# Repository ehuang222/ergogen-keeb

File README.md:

# ergogen-keeb (better name pending)
A 66-key wireless (BLE) ergonomic split mechanical keyboard generated with Ergogen. Heavily inspired by [keyzog's Kapl](https://github.com/keyzog/kapl) and [omkbd's Ergodash](https://github.com/omkbd/ErgoDash) keyboards.

This is a learning project. It's _very_ WIP and my first foray into PCB design and 3D modeling. Be warned, stuff in this repo will likely be broken and messy.

## Table of Contents
- [Project Overview](#project-overview)
- [Resources and Tools](#resources-and-tools)
- [Notes](#notes)

## Project Overview
TODO

## Resources and Tools
- [Ergogen Ceoloide](https://ergogen.ceoloide.com/) - Ceoloide's web-based Ergogen that supports custom footprints
- [ceoloide's ergogen PCB footprints](https://github.com/ceoloide/ergogen-footprints) - Very useful to have this open in a separate tab to reference footprint parameters when using the web-based Ergogen
- [FlatFootFox's Let's Design A Keyboard With Ergogen v4](https://flatfootfox.com/ergogen-introduction/) - The de facto Ergogen guide.
- [easyeda2kicad](https://github.com/uPesy/easyeda2kicad.py) - For downloading LSCS (see JLCPCB parts) footprints and models for use in KiCad
- [KiCad to Ergogen footprint converter](https://kicad2ergogen.genteure.com/) - For converting the abovementioned footprints so they can be used in Ceoloide's Ergogen
- [kicad-druid](https://github.com/Cimos/kicad-druid) - KiCad design rules for JLCPCB and PCBWay, supports KiCad versions 8 through 10
- [KiCad ViaStitching Plugin](https://github.com/weirdgyn/viastitching) - Generates stitching vias over a fill zone.
- [SVG Viewer](https://www.svgviewer.dev/) - A web-based SVG viewer, used this to flip/mirror SVG files.
- [Shaper Utilities](https://marketplace.autodesk.com/apps/1caf9b83-5b54-4cab-b893-9c0b9e8f312a) - Autodesk Fusion plugin for exporting SVGs
- [Joric's nrfmicro wiki - Alternatives](https://github.com/joric/nrfmicro/wiki/Alternatives) - Wiki for Pro Micro Compatible alternatives including the SuperMini NRF52840

## Notes
These are little notes to myself that I found useful (and because if I don't write them down I'll forget them in a week). Sharing these in case they may be useful to someone else.
- [How to View These PCBs With Their 3D Models in KiCad](#how-to-view-these-pcbs-with-their-3d-models-in-kicad)
- [Refining Ergogen Board Outlines in Fusion](#refining-ergogen-board-outlines-in-fusion)
- [How to Import SVG for Board Outline in KiCad](#how-to-import-svg-for-board-outline-in-kicad)

### How to View These PCBs With Their 3D Models in KiCad
Clone/download this repo and note down your local path to the /kicad/easyeda2kicad/ directory.

In KiCad, go to `Preferences` -> `Configure Paths...`. Add a new Environment Variable named `EASYEDA2KICAD` with your local easyeda2kicad/ directory path.

Next, go to `Preferences` -> `Manage Footprint Libraries...`. Add the paths to the easyeda2kicad.3dshapes/ and easyeda2kicad.pretty/ directories.

Next, go to `Preferences` -> `Manage Symbol Libraries...` and add the path to the `easyeda2kicad.kicad_sym` file.

Restart KiCad, then open the PCB files. Click on `3D Viewer` to view the PCB with all its models.

### Refining Ergogen Board Outlines in Fusion

I wanted a curved edge to my PCBs (and key plate) but couldn't find an easy way to do it through KiCad or Ergogen. Then I read that you can do the outline in CAD software then import it into KiCad.

I took the DXFs of the board and plate outlines for one side (`board_left.dxf` and `plate_left.dxf`), created a new part in Fusion, created a sketch for each, then imported the DXFs into their respective sketch. I imported both DXFs because I wanted to easily compare them and make sure my new board edges would not interfere with the switch footprints.

Next, I added a few free-floating reference points above certain key cutouts Then added sketch dimensions from the key to its respective point, setting the dimension to 3.525 mm to match the outer edge widths of the key plate. I didn't want my new curve to go lower than this as I was worried it would make the key plate edges too bendy/fragile. I also needed the space for my PCB routes.

Then I used the Fit Point Spline to create my curved lines. At some points, such as the top corners, the filleted areas needed to be redone to match the new spline. 

Once I was happy, I exported the modified `plate_left` sketch as a DXF for future Fusion use. I then copypasted the plate sketch into a new sketch and removed the key cutouts. 

<details>
<summary>How to Copypaste Fusion Sketches within the Same File</summary>
Edit the sketch that you want to copy from. 

Drag a selection over the entire sketch and `CTRL + C` to copy.

Click `Finish Sketch` to end editing the sketch. 

Then, edit the sketch that you want to paste in. `CTRL + V` to paste your previous selection. Make sure sketch is appropriately aligned.
</details>

I exported the DXF for use as my new `board_left.dxf`. Finally, using Fusion's Shaper Utilities plugin, I exported an SVG for use in KiCad.

### How to Import SVG for Board Outline in KiCad

In KiCad, go to `File` > `Import` > `Graphics`. I selected my SVG and set the import layer to `User.4`. Place it somewhere on the side. I'm placing this outline on the User.4 layer first because I'm using this as a placeholder outline to align my edge cut that's coming up. 

Next, I selected the imported polygon, all the segments should be highlighted, and set the line width to 0.15 mm to match the Ergogen-generated edge cut outline.

On the right, I select the `Edge.Cuts` layer so it's active. Then clicked on the imported polygon and pressed `M` to begin moving it. Move it over the existing outline and it should snap to position right over it (you should see the crosshair icon on the cursor). If it's not snapping, try it at one of the corners.

With the `Edge.Cuts` layer still active, go to `Edit` > `Global Deletions`. Check the box for `Board Outline` and select `Current layer (Edge.Cuts) only`. Click OK and your existing board outline should be deleted.

Import the SVG again but this time choose the `Edge.Cuts` layer.

Update the line widths for this polygon to 0.15 mm like before.

Set the `User.4` layer as active and then move your new board outline over until it snaps onto the `User.4` outline.

Once again, go to `Global Deletions`. Check the box for `Graphics` and select the current layer (`User.4`). Click OK and the placeholder board outline is deleted.

Your new board outline is now in place on the `Edge.Cuts` layer. Refill ground zones and run DRC to verify.

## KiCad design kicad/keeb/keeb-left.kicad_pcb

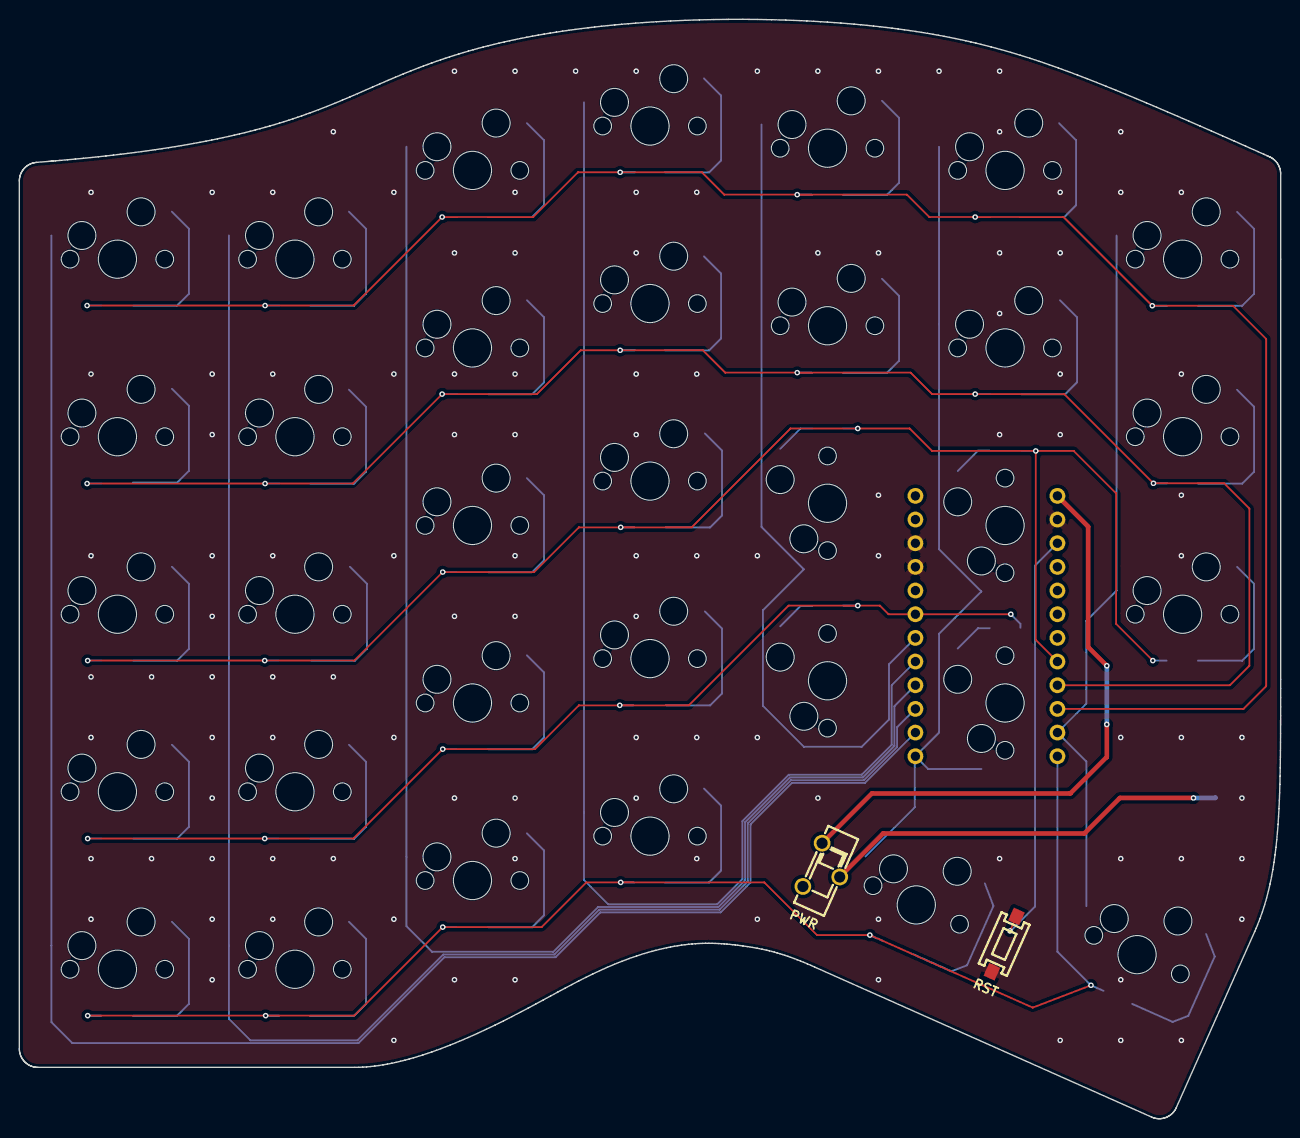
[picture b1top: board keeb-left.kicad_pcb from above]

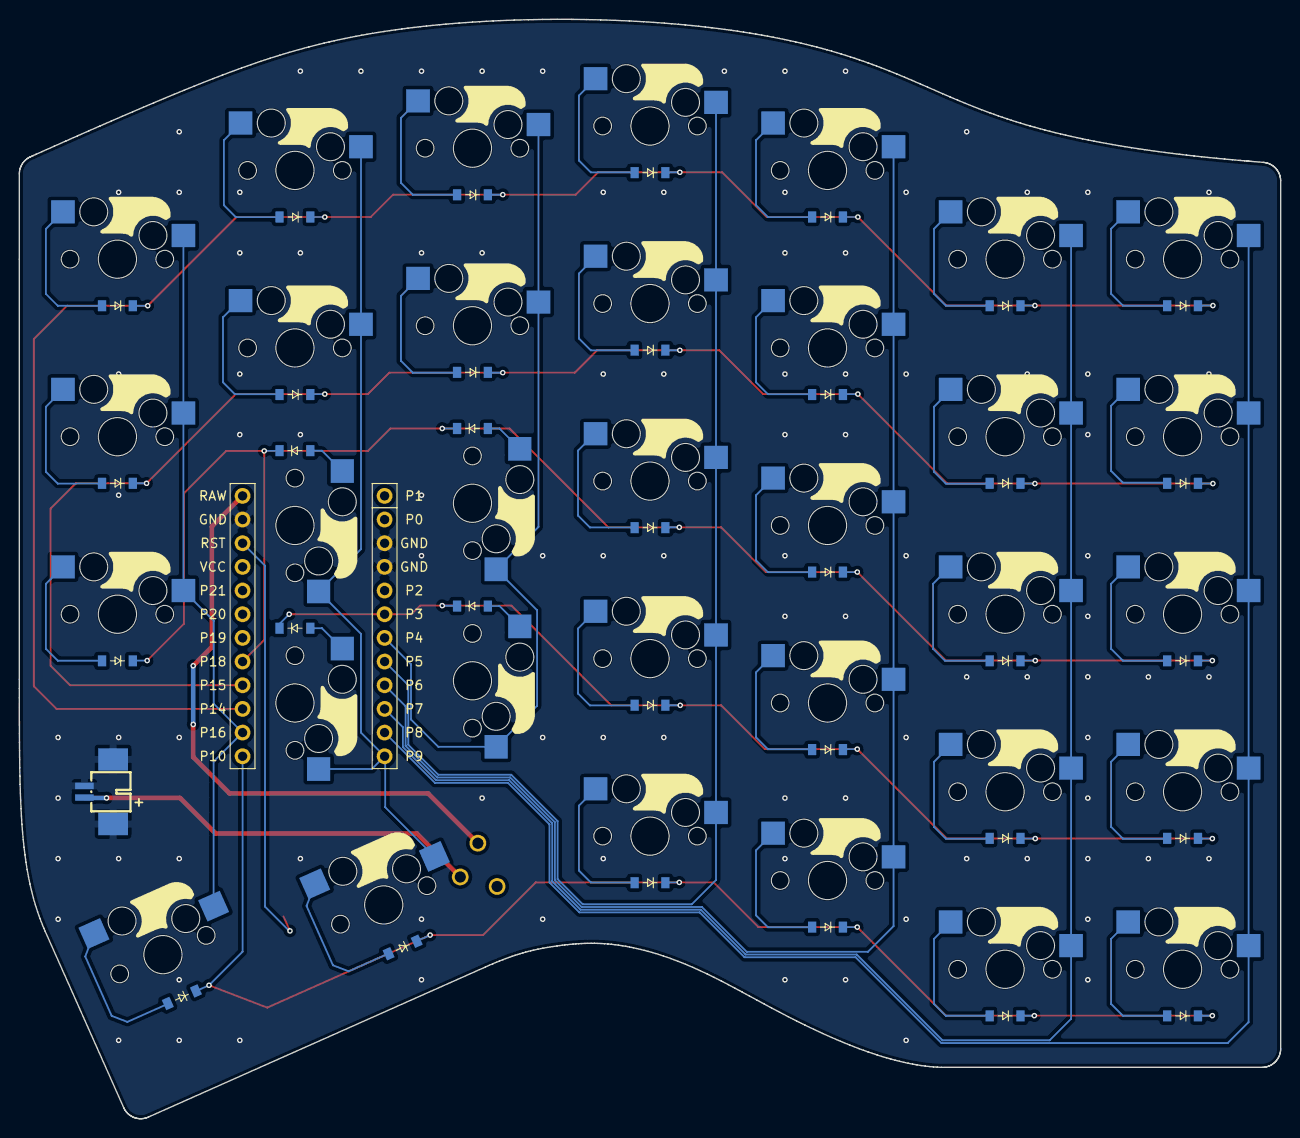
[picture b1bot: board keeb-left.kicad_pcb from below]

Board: 2 copper layers, 135.4 x 118.0 mm, 70 parts (68 on the bottom side), 49 nets.

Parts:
D1, D2, D3, D4, D5, D6, D7, D8, D9, D10, D11, D12, D13, D14, D15, D16, D17, D18, D19, D20, D21, D22, D23, D24, D25, D26, D27, D28, D29, D30, D31, D32, D33: diode_tht_sod123
JST1: CONN-SMD_1.25T-2P-WT
MCU1: mcu_supermini_nrf52840
PWR1: SW-TH_K3-1235D-L1
RST1: KEY-SMD_L6.0-W3.3-LS6.7
S1, S2, S3, S4, S5, S6, S7, S8, S9, S10, S11, S12, S13, S14, S15, S16, S17, S18, S19, S20, S21, S22, S23, S24, S25, S26, S27, S28, S29, S30, S31, S32, S33: switch_mx

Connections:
GND: JST1.1, JST1.3, JST1.4, MCU1.2, MCU1.21, MCU1.22, RST1.1
P3: D2.1, D7.1, D12.1, D17.1, D29.1, D31.1, MCU1.19
P4: MCU1.18, S21.1, S22.1, S28.1, S29.1
P5: MCU1.17, S16.1, S17.1, S18.1, S19.1, S20.1
P6: MCU1.16, S11.1, S12.1, S13.1, S14.1, S15.1
P7: MCU1.15, S6.1, S7.1, S8.1, S9.1, S10.1
P8: MCU1.14, S1.1, S2.1, S3.1, S4.1, S5.1
P9: MCU1.13, S23.1, S24.1, S30.1, S31.1, S32.1
P10: D1.1, D6.1, D11.1, D16.1, D28.1, D33.1, MCU1.12
P14: D5.1, D10.1, D15.1, D20.1, D22.1, D24.1, D27.1, MCU1.10
P15: D4.1, D9.1, D14.1, D19.1, D21.1, D23.1, D26.1, MCU1.9
P16: MCU1.11, S25.1, S26.1, S27.1, S33.1
P18: D3.1, D8.1, D13.1, D18.1, D25.1, D30.1, D32.1, MCU1.8
POS: JST1.2, PWR1.2
RAW: MCU1.1, PWR1.1
RST: MCU1.3, RST1.2
c0_mods: D1.2, S1.2
c0_r0: D5.2, S5.2
c0_r1: D4.2, S4.2
c0_r2: D3.2, S3.2
c0_r3: D2.2, S2.2
c1_mods: D6.2, S6.2
c1_r0: D10.2, S10.2
c1_r1: D9.2, S9.2
c1_r2: D8.2, S8.2
c1_r3: D7.2, S7.2
c2_mods: D11.2, S11.2
c2_r0: D15.2, S15.2
c2_r1: D14.2, S14.2
c2_r2: D13.2, S13.2
c2_r3: D12.2, S12.2
c3_mods: D16.2, S16.2
c3_r0: D20.2, S20.2
c3_r1: D19.2, S19.2
c3_r2: D18.2, S18.2
c3_r3: D17.2, S17.2
c4_r0: D22.2, S22.2
c4_r1: D21.2, S21.2
c4_r2: D30.2, S29.2
c4_r3: D29.2, S28.2
c5_r0: D24.2, S24.2
c5_r1: D23.2, S23.2
c5_r2: D32.2, S31.2
c5_r3: D31.2, S30.2
c6_r0: D27.2, S27.2
c6_r1: D26.2, S26.2
c6_r2: D25.2, S25.2
t0_r0: D28.2, S32.2
t1_r0: D33.2, S33.2

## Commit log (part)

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2026-06-01 Initial commit of ergogen files
2026-06-01 Updating thumbfan spacing
2026-06-03 Added enclosed case outline
2026-06-03 Removing extra outlines
2026-06-04 Updating Ergogen outputs
2026-06-06 Updating PCB footprints and nets
2026-06-07 Updating PCB and generated file outputs
2026-06-08 Updating net assignments for improved routing
2026-06-11 Adding routed left PCB
2026-06-11 Adding routed right PCB
2026-06-22 Adding additional outlines for Fusion work, updated MCU placement on PCBs, updated routing to accomodate
